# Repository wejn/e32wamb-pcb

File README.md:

# Hue White Ambiance replacement using ESP32

**Note: This is work in progress, not guaranteed to be usable.**

This will be a pcb for my Hue White Ambiance replacement driver
suitable for my "Beng Ceiling Light" from Philips.

For background info see
[Reversing Philips Hue light driver](https://wejn.org/2024/12/reversing-philips-hue-light-driver/),
or directly the [Final stretch for e32wamb: PCB, cables, antenna
holder](https://wejn.org/2025/05/finishing-stretch-for-e32wamb-pcb-cables-antenna-holder/)
post that discusses the PCB in particular.

## Pretty pictures

## License

See the `LICENSE.md` file (tl;dr: CC BY-SA 4.0 for anything by me)

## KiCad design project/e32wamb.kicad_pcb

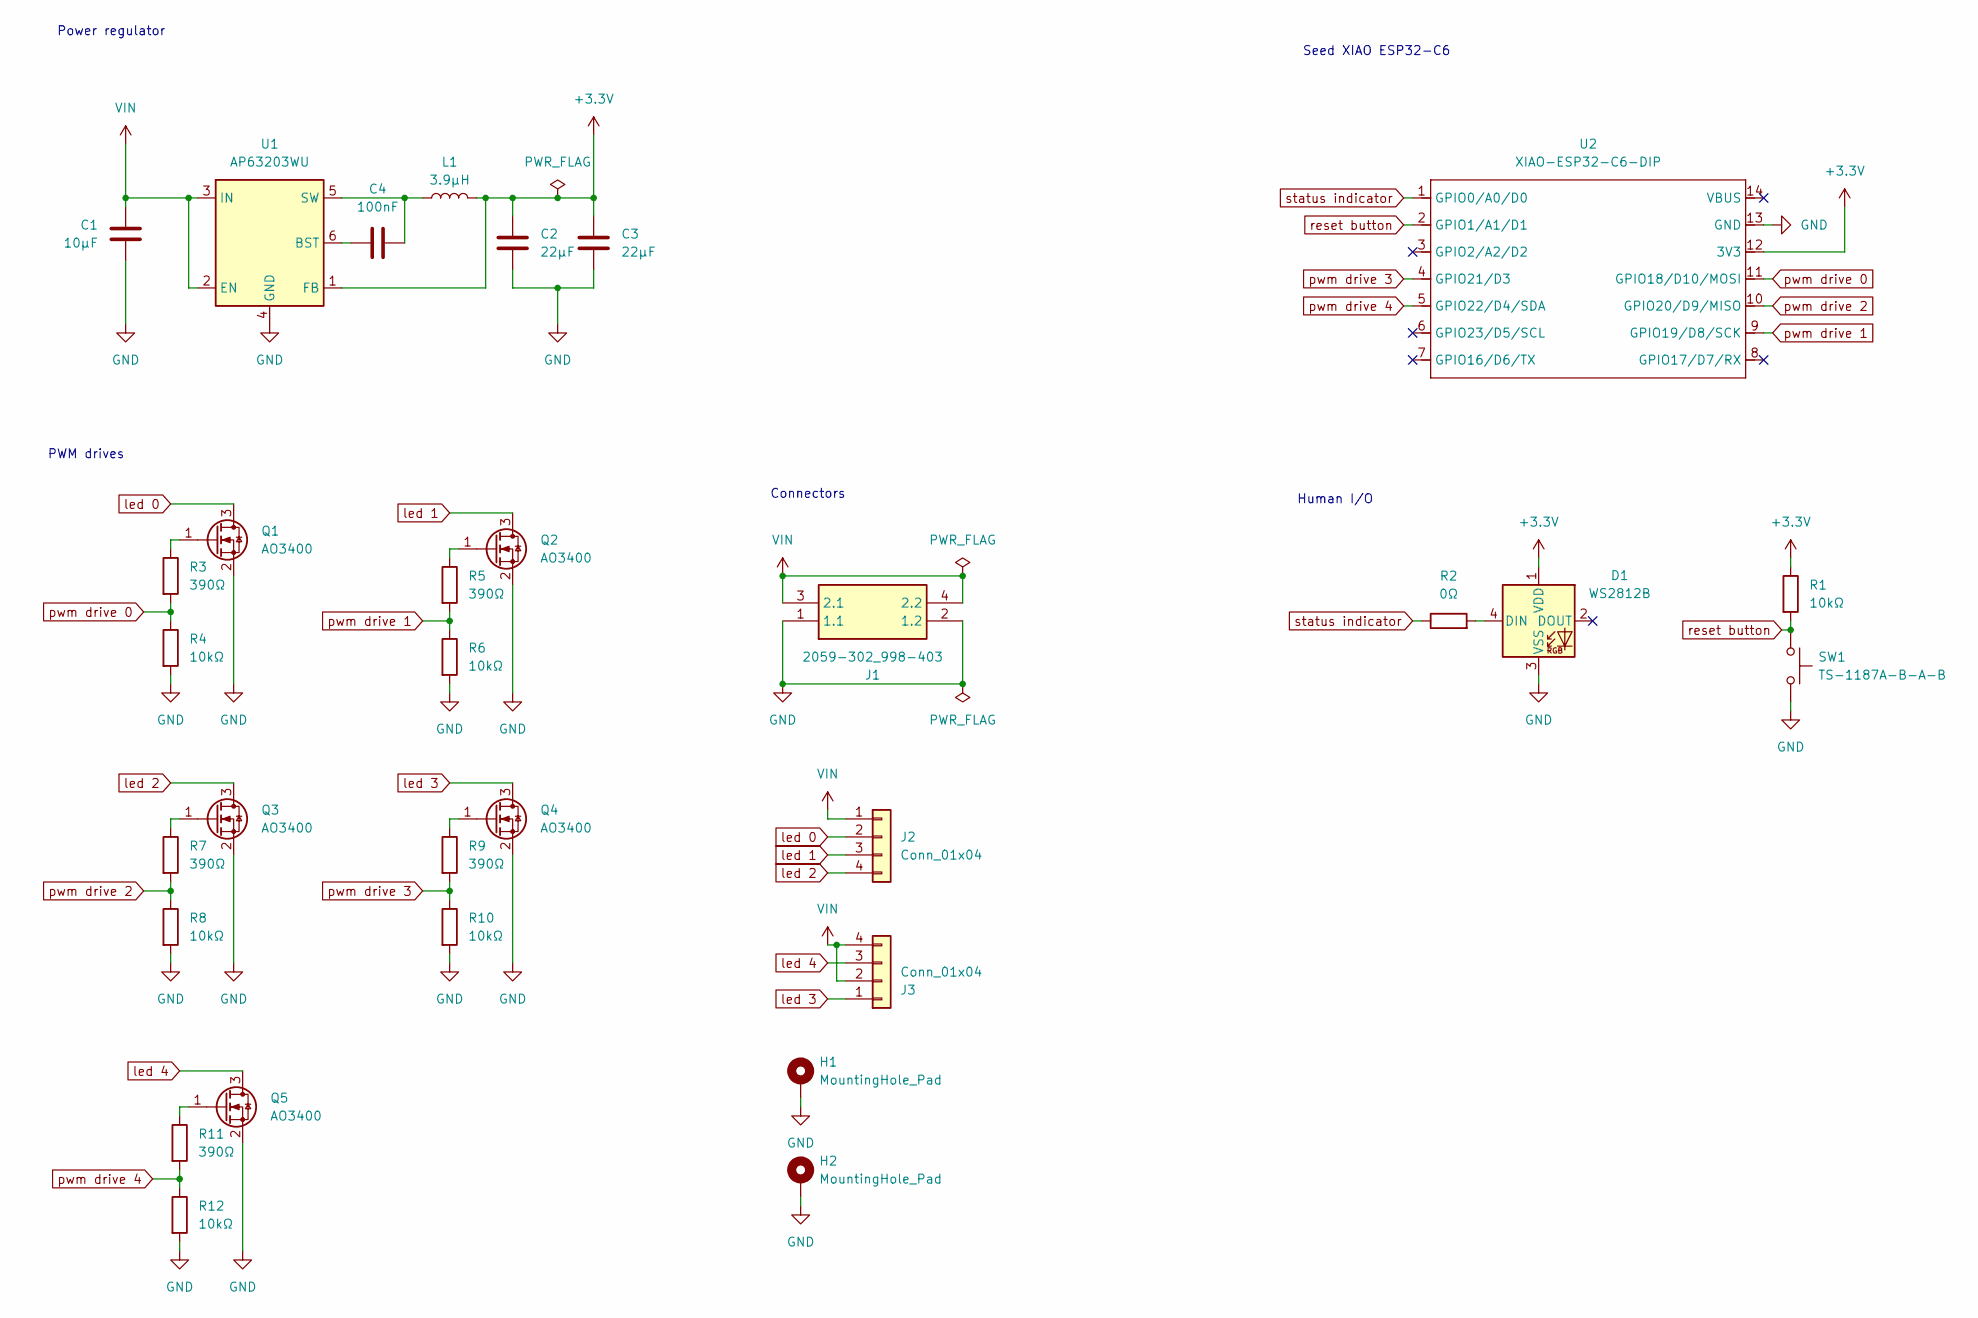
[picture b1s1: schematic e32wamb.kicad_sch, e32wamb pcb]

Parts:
C1: 10μF; C_1206_3216Metric; LCSC C13585
C2, C3: 22μF; C_0603_1608Metric; LCSC C59461
C4: 100nF; C_0603_1608Metric; LCSC C14663
D1: WS2812B; LED_WS2812B_PLCC4_5.0x5.0mm_P3.2mm; LCSC C2920042
H1, H2: MountingHole_Pad; MountingHole_3.2mm_M3_ISO14580_Pad
J1: 2059-302_998-403; 2059302998403; Manufacturer_Part_Number 2059-302/998-403; LCSC C2765060
J2: Conn_01x04; JST_PH_S4B-PH-SM4-TB_1x04-1MP_P2.00mm_Horizontal; Manufacturer_Part_Number S4B-PH-SM4-TB; LCSC C265102
J3: Conn_01x04; JST_PH_S4B-PH-SM4-TB_1x04-1MP_P2.00mm_Horizontal; Manufacturer_Part_Number S3B-PH-SM4-TB; LCSC C265102
L1: 3.9μH; L_Sunlord_SWPA4030S; PartNo SWPA4030S3R9MT; LCSC C96899
Q1, Q2, Q3, Q4, Q5: AO3400; SOT-23; LCSC C4748804
R1, R4, R6, R8, R10, R12: 10kΩ; R_0603_1608Metric; LCSC C25804
R2: 0Ω; R_0603_1608Metric; LCSC C21189
R3, R5, R7, R9, R11: 390Ω; R_0603_1608Metric; LCSC C23151
SW1: TS-1187A-B-A-B; SW_Push_1P1T_XKB_TS-1187A; LCSC C318884
U1: AP63203WU; TSOT-23-6; LCSC C780769
U2: XIAO-ESP32-C6-DIP; XIAO-ESP32C6-DIP

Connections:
+3.3V: C2.1, C3.1, D1.1 (VDD), L1.2, R1.1, U1.1 (FB), U2.12 (3V3)
GND: C1.2, C2.2, C3.2, D1.3 (VSS), H1.1, H2.1, J1.1 (1.1), J1.2 (1.2), Q1.2 (S), Q2.2 (S), Q3.2 (S), Q4.2 (S), Q5.2 (S), R4.2, R6.2, R8.2, R10.2, R12.2, SW1.2, U1.4 (GND), U2.13 (GND)
unnamed: D1.4 (DIN), R2.2
unnamed: Q1.1 (G), R3.1
unnamed: Q2.1 (G), R5.1
unnamed: Q3.1 (G), R7.1
unnamed: Q4.1 (G), R9.1
unnamed: Q5.1 (G), R11.1
unnamed: C4.2, U1.6 (BST)
unnamed: C4.1, L1.1, U1.5 (SW)
VIN: C1.1, J1.3 (2.1), J1.4 (2.2), J2.1, J3.2, J3.4, U1.2 (EN), U1.3 (IN)
led 0: J2.2, Q1.3 (D)
led 1: J2.3, Q2.3 (D)
led 2: J2.4, Q3.3 (D)
led 3: J3.1, Q4.3 (D)
led 4: J3.3, Q5.3 (D)
pwm drive 0: R3.2, R4.1, U2.11 (GPIO18/D10/MOSI)
pwm drive 1: R5.2, R6.1, U2.9 (GPIO19/D8/SCK)
pwm drive 2: R7.2, R8.1, U2.10 (GPIO20/D9/MISO)
pwm drive 3: R9.2, R10.1, U2.4 (GPIO21/D3)
pwm drive 4: R11.2, R12.1, U2.5 (GPIO22/D4/SDA)
reset button: R1.2, SW1.1, U2.2 (GPIO1/A1/D1)
status indicator: R2.1, U2.1 (GPIO0/A0/D0)

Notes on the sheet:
Human I/O
PWM drives
Connectors
Seed XIAO ESP32-C6
Power regulator

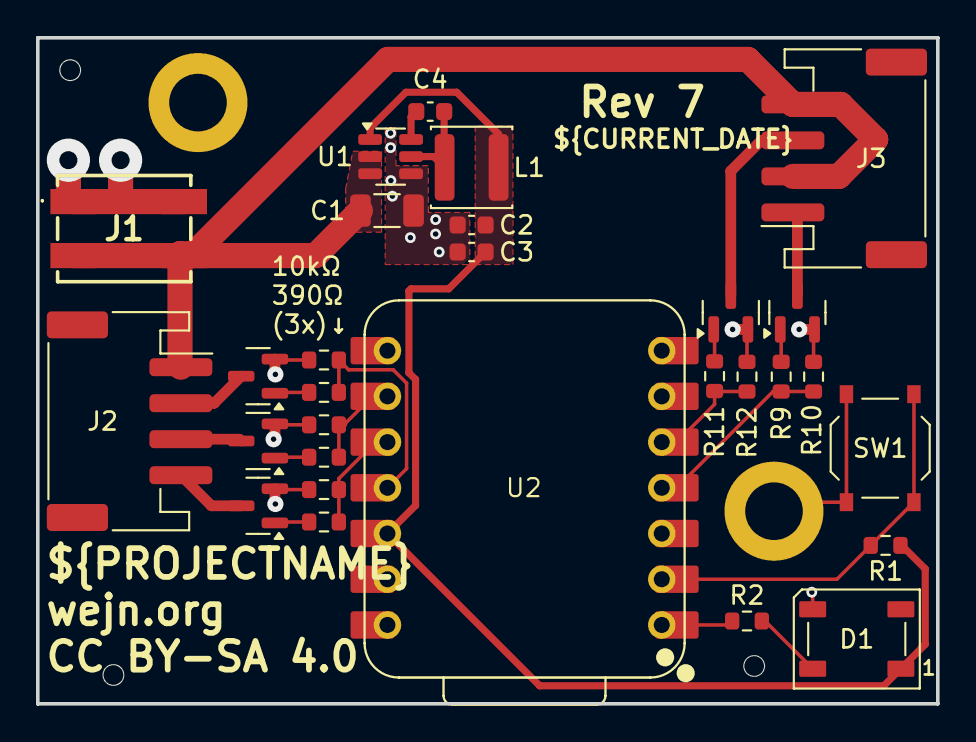
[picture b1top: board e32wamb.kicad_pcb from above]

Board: 2 copper layers, 50.0 x 37.0 mm, 31 parts (0 on the bottom side), 23 nets.

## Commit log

2025-04-05 Initial commit: datasheets + schematic
2025-04-05 Update xiao (don't place, add ds+source)
2025-04-05 Add license
2025-04-05 Unfuckulate .gitignore, push missing assets
2025-04-05 Fix name of Seeed Studio
2025-04-05 Remove New_Library :-)
2025-04-05 Add ohm symbol to all Rs, add license info
2025-04-05 Add 3d models, smaller wago, mounting holes
2025-04-06 Ignore yet another autosave
2025-04-06 Superficial changes to project (auto?)
2025-04-06 Flip connector, fix mosfet type and footprint
2025-04-06 First shot at the pcb (layout only, no wiring yet)
2025-04-08 First shot at wiring (complete pcb)
2025-04-08 Fix mounting hole h2 footprint
2025-04-08 Add readme
2025-04-09 Add lcsc part number for smaller wago
2025-04-09 Oops: c2,c3 were wrong footprint (lcsc num)
2025-04-09 Ignore production files
2025-04-09 Add jlcpcb tooling holes
2025-04-09 Oops: c2,c3 were wrong lcsc num, even on pcb
2025-04-09 Purge fp-info-cache and *.kicad_prl
2025-04-09 Add rotation offset for U1 (for jlcfab), bump revision
2025-04-09 Add pics, Makefile, jlc-fab-toolkit
2025-04-10 Tune spacing between mounting holes; switch to vars for revision + date
2025-04-11 Add keepout zone around the antenna
    I thought I could do without because I'll be using an external antenna,
    but it hardly costs anything. So why not have the keepout just in case.
2025-04-13 More space around J3, thicker VIN for buck
    Based on Sam's review.
2025-04-13 Switch the esp32-c6 to DIP footprint
    Sam suggested it might make the debugging a bit easier.
2025-04-13 Slightly increase the keepout around antenna
2025-04-13 Switch J3 to 4-pin JST PH
    Not only will that give me two additional independent chans, but
    also one less BOM part to deal with (cheaper for PCBA).
2025-04-15 Fix wrong J3 LCSC part number
    Forgot to fix this in 7358522f.
2025-05-11 Add blog post link

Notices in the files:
project/e32wamb.kicad_pcb:
Licensed under CC BY-SA 4.0
